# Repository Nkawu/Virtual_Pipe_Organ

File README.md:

# Virtual Pipe Organ

Project documented at https://hackaday.io/project/19077-virtual-pipe-organ

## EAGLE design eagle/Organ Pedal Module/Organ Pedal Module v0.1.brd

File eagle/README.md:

Eagle CAD design files for modules used in the virtual organ

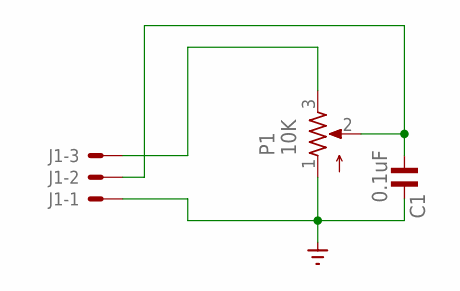
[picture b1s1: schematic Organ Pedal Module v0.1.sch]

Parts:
C1: 0.1uF; C0805MP
J1: 22-05-7038-03; 7395-03
P1: 10K; PTA6043

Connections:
GND: C1.2, J1.1, P1.1
unnamed: J1.3, P1.3
unnamed: C1.1, J1.2, P1.2

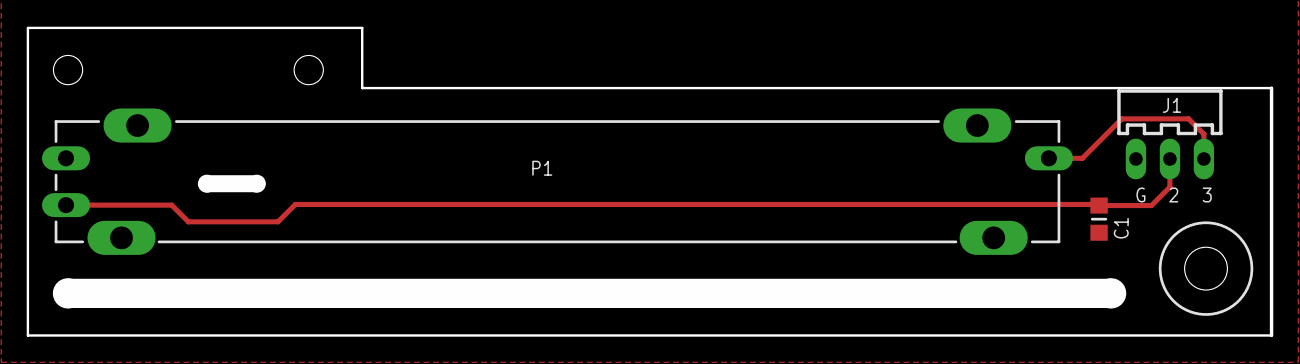
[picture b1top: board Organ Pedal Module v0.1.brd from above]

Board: 2 copper layers, 91.0 x 21.0 mm, 4 parts (0 on the bottom side), 3 nets.

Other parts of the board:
U$1: 3,2

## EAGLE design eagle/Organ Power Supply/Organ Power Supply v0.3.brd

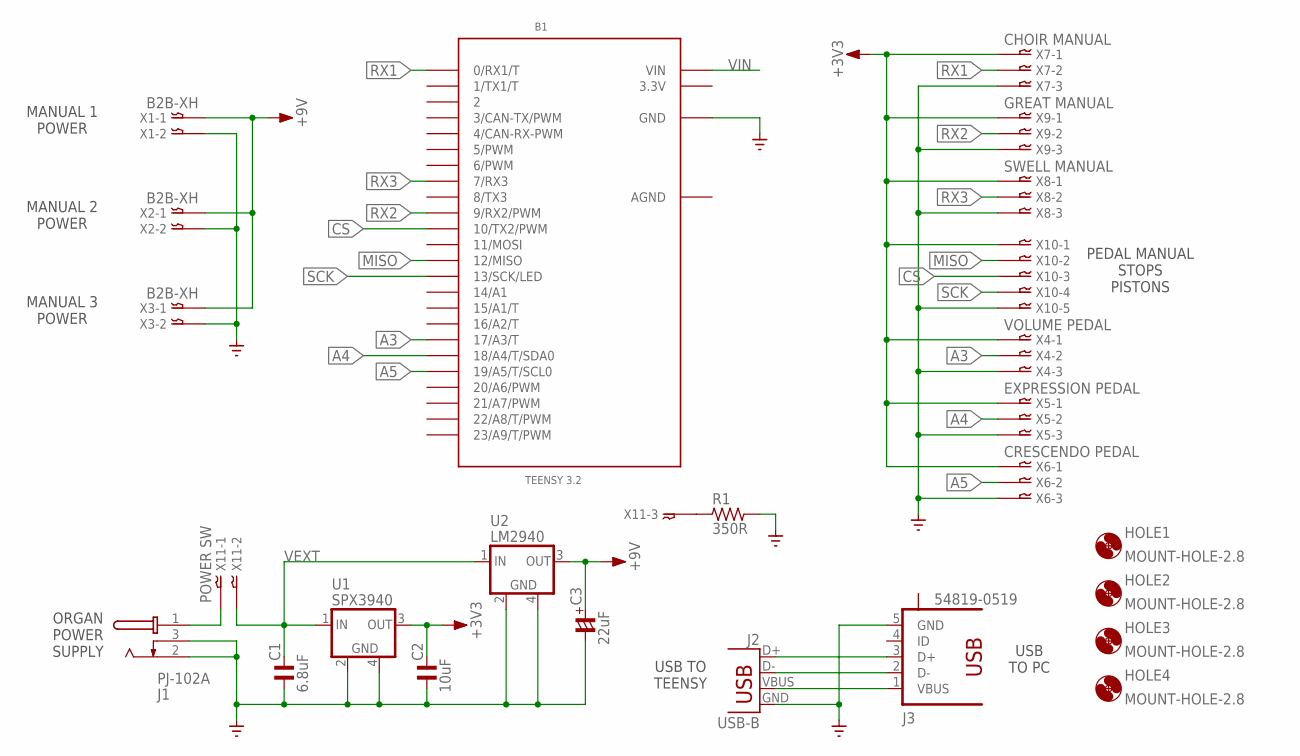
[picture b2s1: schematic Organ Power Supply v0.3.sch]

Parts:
B1: TEENSY 3.2; TEENSY3-DIL
C1: 6.8uF; C1206MP
C2: 10uF; C0805MP
C3: 22uF; C3216-18R/T
HOLE1, HOLE2, HOLE3, HOLE4: MOUNT-HOLE-2.8; 2,8
J1: PJ-102A; PJ-102XH
J2: USB-B; USB-B-PTH
J3: 54819-0519
R1: 350R; R0805MP
U1: SPX3940; SOT223
U2: LM2940; SOT223
X1, X2, X3: B2B-XH; B2B-XH-A
X4: VOLUME PEDAL; B3B-XH
X5: EXPRESSION PEDAL; B3B-XH
X6: CRESCENDO PEDAL; B3B-XH
X7: CHOIR MANUAL; B3B-XH
X8: SWELL MANUAL; B3B-XH
X9: GREAT MANUAL; B3B-XH
X10: 05-JST-B5B-XH-A; B5B-XH
X11: POWER SW; B3B-XH

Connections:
3.3V: B1.3.3V
+3V3: C2.2, U1.3 (OUT), X4.P$1, X5.P$1, X6.P$1, X7.P$1, X8.P$1, X9.P$1, X10.P$1
+9V: C3.+, U2.3 (OUT), X1.P$1, X2.P$1, X3.P$1
A3: B1.17/A3 (17/A3/T), X4.P$2
A4: B1.18/A4 (18/A4/T/SDA0), X5.P$2
A5: B1.19/A5 (19/A5/T/SCL0), X6.P$2
AGND: B1.AGND
CS: B1.10 (10/TX2/PWM), X10.P$3
GND: B1.GND, C1.1, C2.1, C3.-, J1.2 (S), J1.3 (SS), J2.GND, J3.5 (GND), R1.2, U1.2 (GND), U1.4 (GND), U2.2 (GND), U2.4 (GND), X1.P$2, X2.P$2, X3.P$2, X4.P$3, X5.P$3, X6.P$3, X7.P$3, X8.P$3, X9.P$3, X10.P$5
MISO: B1.12 (12/MISO), X10.P$2
unnamed: J2.VBUS, J3.1 (VBUS)
unnamed: J1.1 (T), X11.P$1
unnamed: R1.1, X11.P$3
unnamed: J2.D+, J3.3 (D+)
unnamed: J2.D-, J3.2 (D-)
RX1: B1.0 (0/RX1/T), X7.P$2
RX2: B1.9 (9/RX2/PWM), X9.P$2
RX3: B1.7 (7/RX3), X8.P$2
SCK: B1.13 (13/SCK/LED), X10.P$4
VEXT: C1.2, U1.1 (IN), U2.1 (IN), X11.P$2
VIN: B1.VIN

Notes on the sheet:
PEDAL MANUAL STOPS PISTONS
MANUAL 1 POWER
MANUAL 2 POWER
MANUAL 3 POWER
ORGAN POWER SUPPLY
USB TO PC
USB TO TEENSY

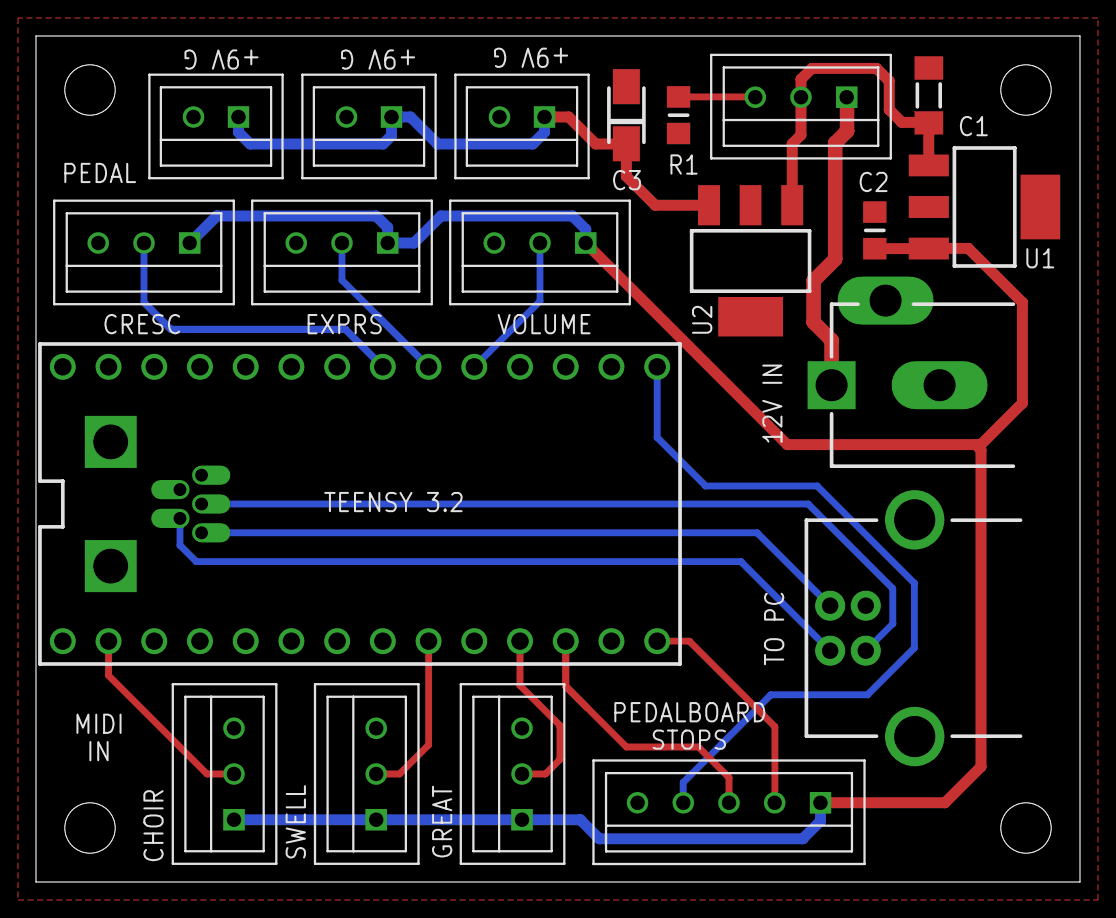
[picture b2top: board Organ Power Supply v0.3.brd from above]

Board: 2 copper layers, 58.0 x 47.0 mm, 25 parts (1 on the bottom side), 18 nets.

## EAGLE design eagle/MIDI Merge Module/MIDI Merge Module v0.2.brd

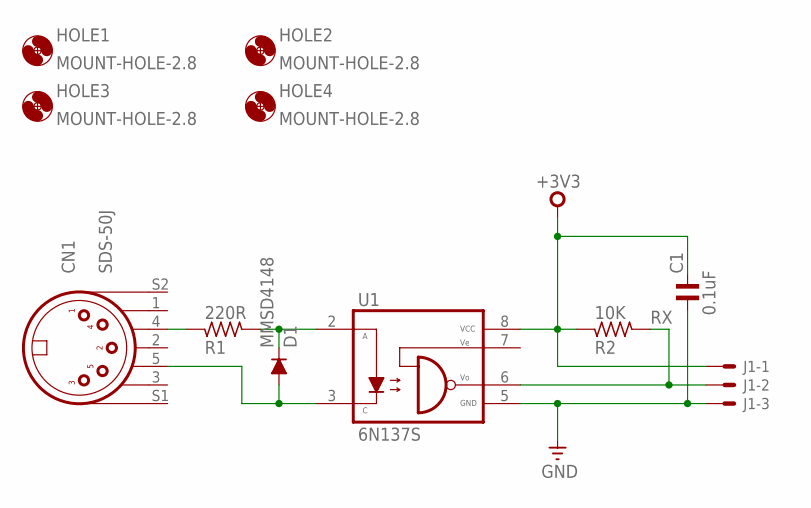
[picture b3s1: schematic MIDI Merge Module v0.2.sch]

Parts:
C1: 0.1uF; C1206MP
CN1: SDS-50J
D1: MMSD4148; SOD123
HOLE1, HOLE2, HOLE3, HOLE4: MOUNT-HOLE-2.8; 2,8
J1: 22-05-7038-03; 7395-03
R1: 220R; R0805MP
R2: 10K; R0805MP
U1: 6N137S; SMD8

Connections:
+3V3: C1.2, J1.1, R2.1, U1.8 (VCC)
GND: C1.1, J1.3, U1.5 (GND)
unnamed: CN1.4, R1.1
unnamed: D1.C, R1.2, U1.2 (A)
unnamed: CN1.5, D1.A, U1.3 (C)
RX: J1.2, R2.2, U1.6 (VO)

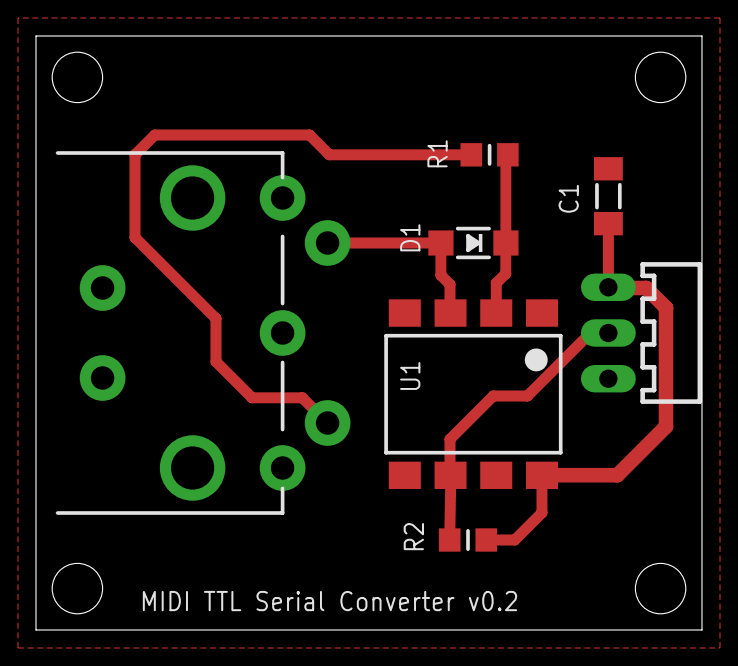
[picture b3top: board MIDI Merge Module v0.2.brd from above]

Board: 2 copper layers, 37.0 x 33.0 mm, 11 parts (0 on the bottom side), 6 nets.

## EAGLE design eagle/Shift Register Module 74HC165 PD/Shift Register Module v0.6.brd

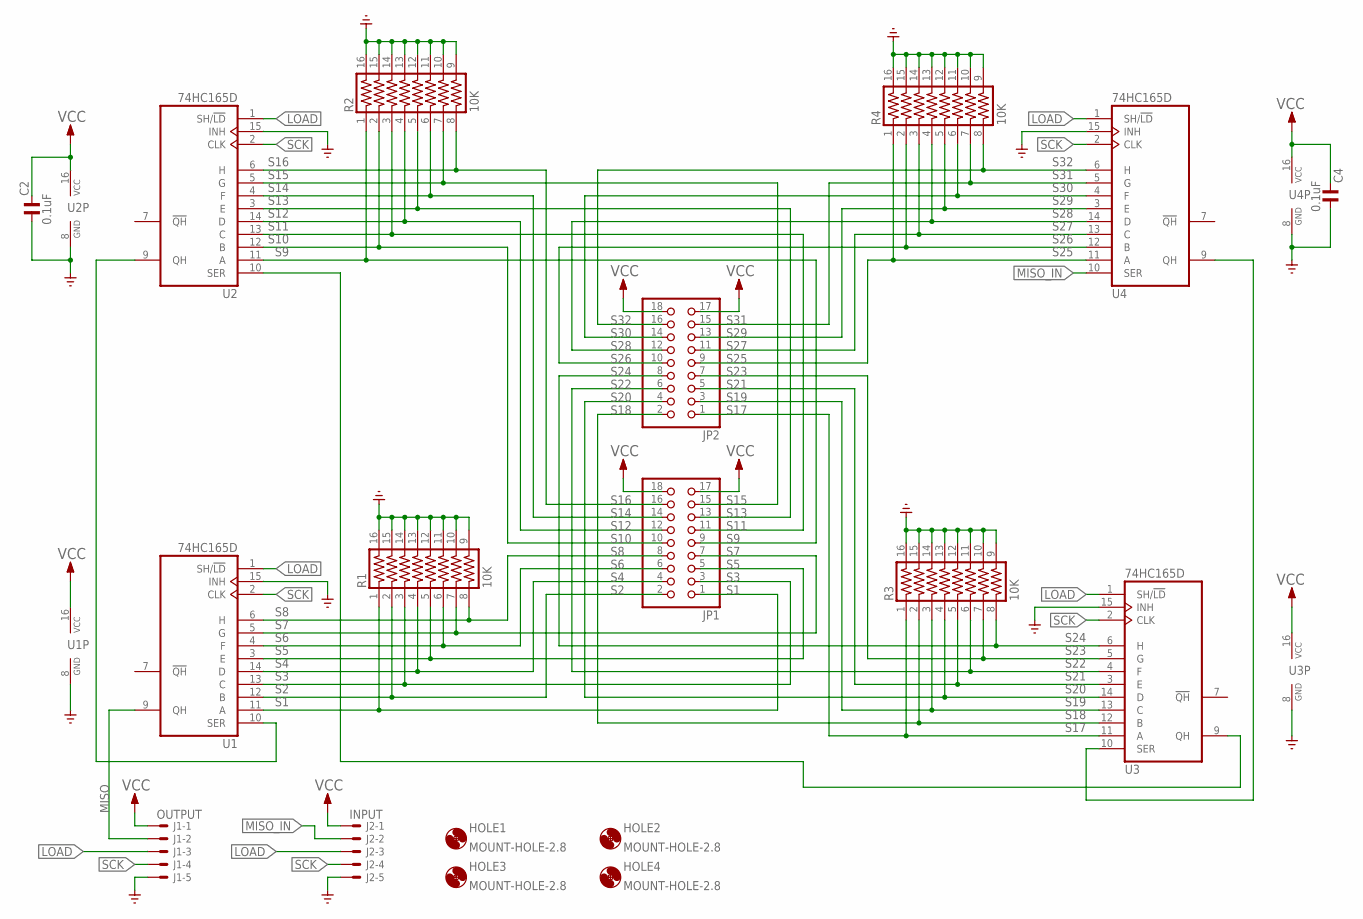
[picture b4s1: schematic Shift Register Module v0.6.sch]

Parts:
C2, C4: 0.1uF; C0805MP
HOLE1, HOLE2, HOLE3, HOLE4: MOUNT-HOLE-2.8; 2,8
J1: OUTPUT; 7395-05
J2: INPUT; 7395-05
JP1, JP2: PINHD-2X9-SHROUDED; 2X09
R1, R2, R3, R4: 10K; 4816P
U1, U2, U3, U4: 74HC165D; SO16

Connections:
GND: C2.1, C4.1, J1.5, J2.5, R1.9, R1.10, R1.11, R1.12, R1.13, R1.14, R1.15, R1.16, R2.9, R2.10, R2.11, R2.12, R2.13, R2.14, R2.15, R2.16, R3.9, R3.10, R3.11, R3.12, R3.13, R3.14, R3.15, R3.16, R4.9, R4.10, R4.11, R4.12, R4.13, R4.14, R4.15, R4.16, U1.8 (GND), U1.15 (INH), U2.8 (GND), U2.15 (INH), U3.8 (GND), U3.15 (INH), U4.8 (GND), U4.15 (INH)
LOAD: J1.3, J2.3, U1.1 (SH/!LD), U2.1 (SH/!LD), U3.1 (SH/!LD), U4.1 (SH/!LD)
MISO: J1.2, U1.9 (QH)
MISO_IN: J2.2, U4.10 (SER)
unnamed: U1.10 (SER), U2.9 (QH)
unnamed: U2.10 (SER), U3.9 (QH)
S1: JP1.1, R1.1, U1.11 (A)
S2: JP1.2, R1.2, U1.12 (B)
S3: JP1.3, R1.3, U1.13 (C)
S4: JP1.4, R1.4, U1.14 (D)
S5: JP1.5, R1.5, U1.3 (E)
S6: JP1.6, R1.6, U1.4 (F)
S7: JP1.7, R1.7, U1.5 (G)
S8: JP1.8, R1.8, U1.6 (H)
S9: JP1.9, R2.1, U2.11 (A)
S10: JP1.10, R2.2, U2.12 (B)
S11: JP1.11, R2.3, U2.13 (C)
S12: JP1.12, R2.4, U2.14 (D)
S13: JP1.13, R2.5, U2.3 (E)
S14: JP1.14, R2.6, U2.4 (F)
S15: JP1.15, R2.7, U2.5 (G)
S16: JP1.16, R2.8, U2.6 (H)
S17: JP2.1, R3.1, U3.11 (A)
S18: JP2.2, R3.2, U3.12 (B)
S19: JP2.3, R3.3, U3.13 (C)
S20: JP2.4, R3.4, U3.14 (D)
S21: JP2.5, R3.5, U3.3 (E)
S22: JP2.6, R3.6, U3.4 (F)
S23: JP2.7, R3.7, U3.5 (G)
S24: JP2.8, R3.8, U3.6 (H)
S25: JP2.9, R4.1, U4.11 (A)
S26: JP2.10, R4.2, U4.12 (B)
S27: JP2.11, R4.3, U4.13 (C)
S28: JP2.12, R4.4, U4.14 (D)
S29: JP2.13, R4.5, U4.3 (E)
S30: JP2.14, R4.6, U4.4 (F)
S31: JP2.15, R4.7, U4.5 (G)
S32: JP2.16, R4.8, U4.6 (H)
SCK: J1.4, J2.4, U1.2 (CLK), U2.2 (CLK), U3.2 (CLK), U4.2 (CLK)
VCC: C2.2, C4.2, J1.1, J2.1, JP1.17, JP1.18, JP2.17, JP2.18, U1.16 (VCC), U2.16 (VCC), U3.16 (VCC), U4.16 (VCC)
XX: U3.10 (SER), U4.9 (QH)

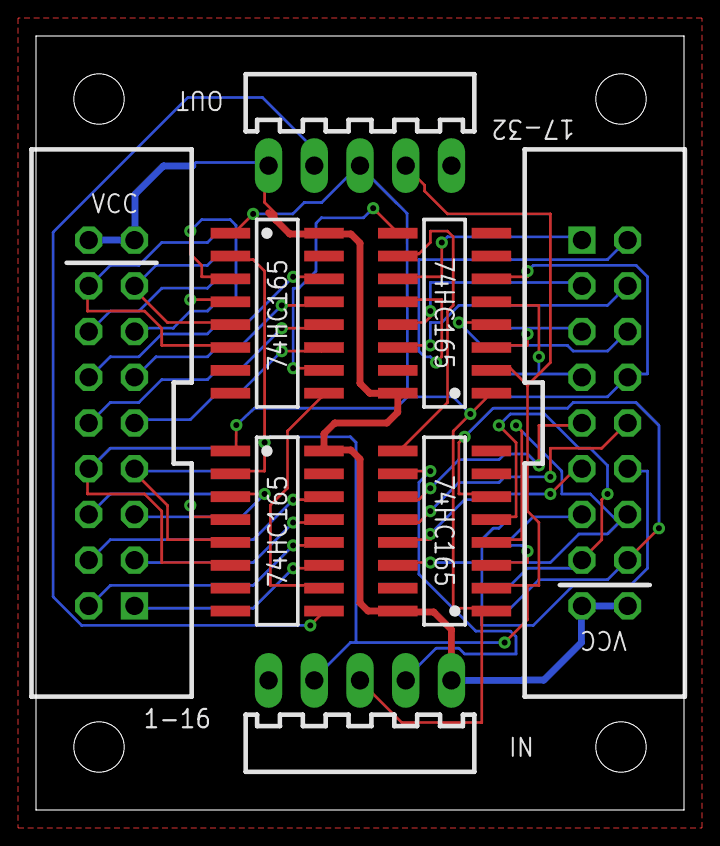
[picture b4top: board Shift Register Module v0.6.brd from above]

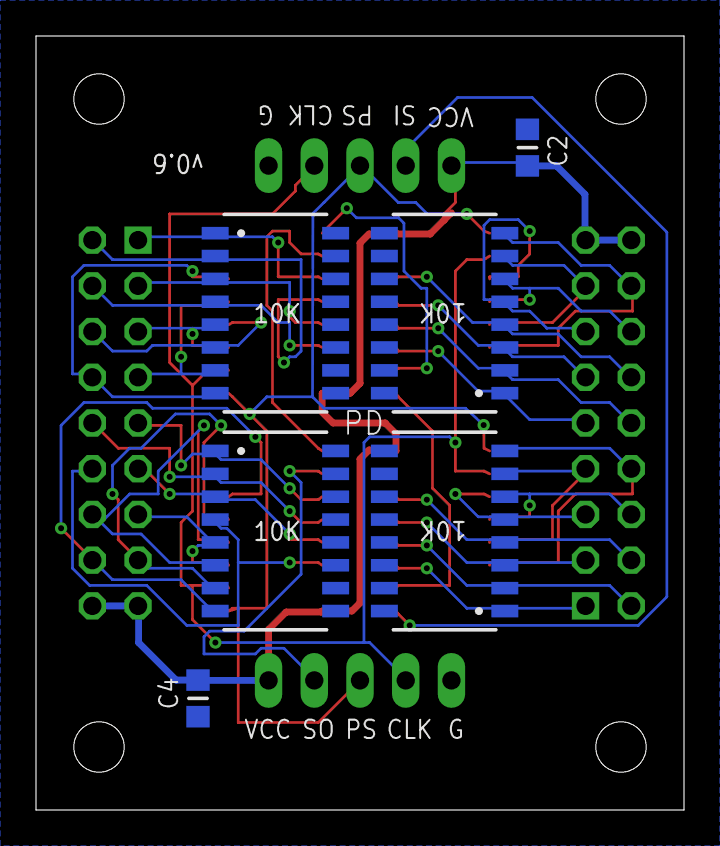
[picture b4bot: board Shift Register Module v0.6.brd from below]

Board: 2 copper layers, 36.0 x 43.0 mm, 18 parts (6 on the bottom side), 41 nets.

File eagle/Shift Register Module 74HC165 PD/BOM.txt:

Shift Register Module 74HC165 PD

Sch:Name	Sch:Value	Sch:Device	Sch:Package	Sch:Description
C2	0.1uF	C_0805MP	C0805MP	NON-POLARIZED CAP
C4	0.1uF	C_0805MP	C0805MP	NON-POLARIZED CAP
J1	OUTPUT	22-05-7058-05	7395-05	CONNECTOR
J2	INPUT	22-05-7058-05	7395-05	CONNECTOR
JP1		PINHD-2X9-SHROUDED	2X09	PIN HEADER
JP2		PINHD-2X9-SHROUDED	2X09	PIN HEADER
R1	10K	4816P-T01	4816P	BOURNS RESISTOR NETWORK
R2	10K	4816P-T01	4816P	BOURNS RESISTOR NETWORK
R3	10K	4816P-T01	4816P	BOURNS RESISTOR NETWORK
R4	10K	4816P-T01	4816P	BOURNS RESISTOR NETWORK
U1	74HC165D	74HC165D	SO16	8-bit parallel load SHIFT REGISTER
U2	74HC165D	74HC165D	SO16	8-bit parallel load SHIFT REGISTER
U3	74HC165D	74HC165D	SO16	8-bit parallel load SHIFT REGISTER
U4	74HC165D	74HC165D	SO16	8-bit parallel load SHIFT REGISTER

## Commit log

2020-05-01 Update eagle repos
2020-05-01 Add Teensy source
2020-05-01 Add BOMs
2020-05-02 Add Digikey part numbers to BOM

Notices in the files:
parts and their libraries:
rc-master: Copyright (C) 2007-2008, Bob Starr
SparkFun-Connectors: Licensing: Creative Commons ShareAlike 4.0 International - https://creativecommons.org/licenses/by-sa/4.0
con-usb: Copyright (C) 2008, Bob Starr
supply1: Copyright (C) 2007, Bob Starr
